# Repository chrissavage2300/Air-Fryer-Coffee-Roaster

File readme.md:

A DIY Coffee roaster based on on air fryer. 

The idea is to have a rotating drum with a heater and fan inside. A nextion display will be used. 

Features:
Adjustable Temp
Adjustable Drum Speed
Adjustable Fan Speed
Cooling and heating modes

Change Log:

The roaster does work, but it has a slight issue when it gets hot where the rotation motor just doesnt turn. From what I can tell, its not a failure of the motor, but a fail in the comms. I have to look into why it does this, as i think its a buffer situation. Everything else works though, so Im not sure why just that gives out. 

10/7/2023- Uploaded Main Code

12/3/2022- Start of this github. But the project dates back a few months atleast

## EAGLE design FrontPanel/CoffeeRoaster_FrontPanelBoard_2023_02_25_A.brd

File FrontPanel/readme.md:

These are the files for the front panel. It mostly works. This communicates with the main panel via USART as it was the only means of communication that was available. 

Latest Version: 6/15/2023

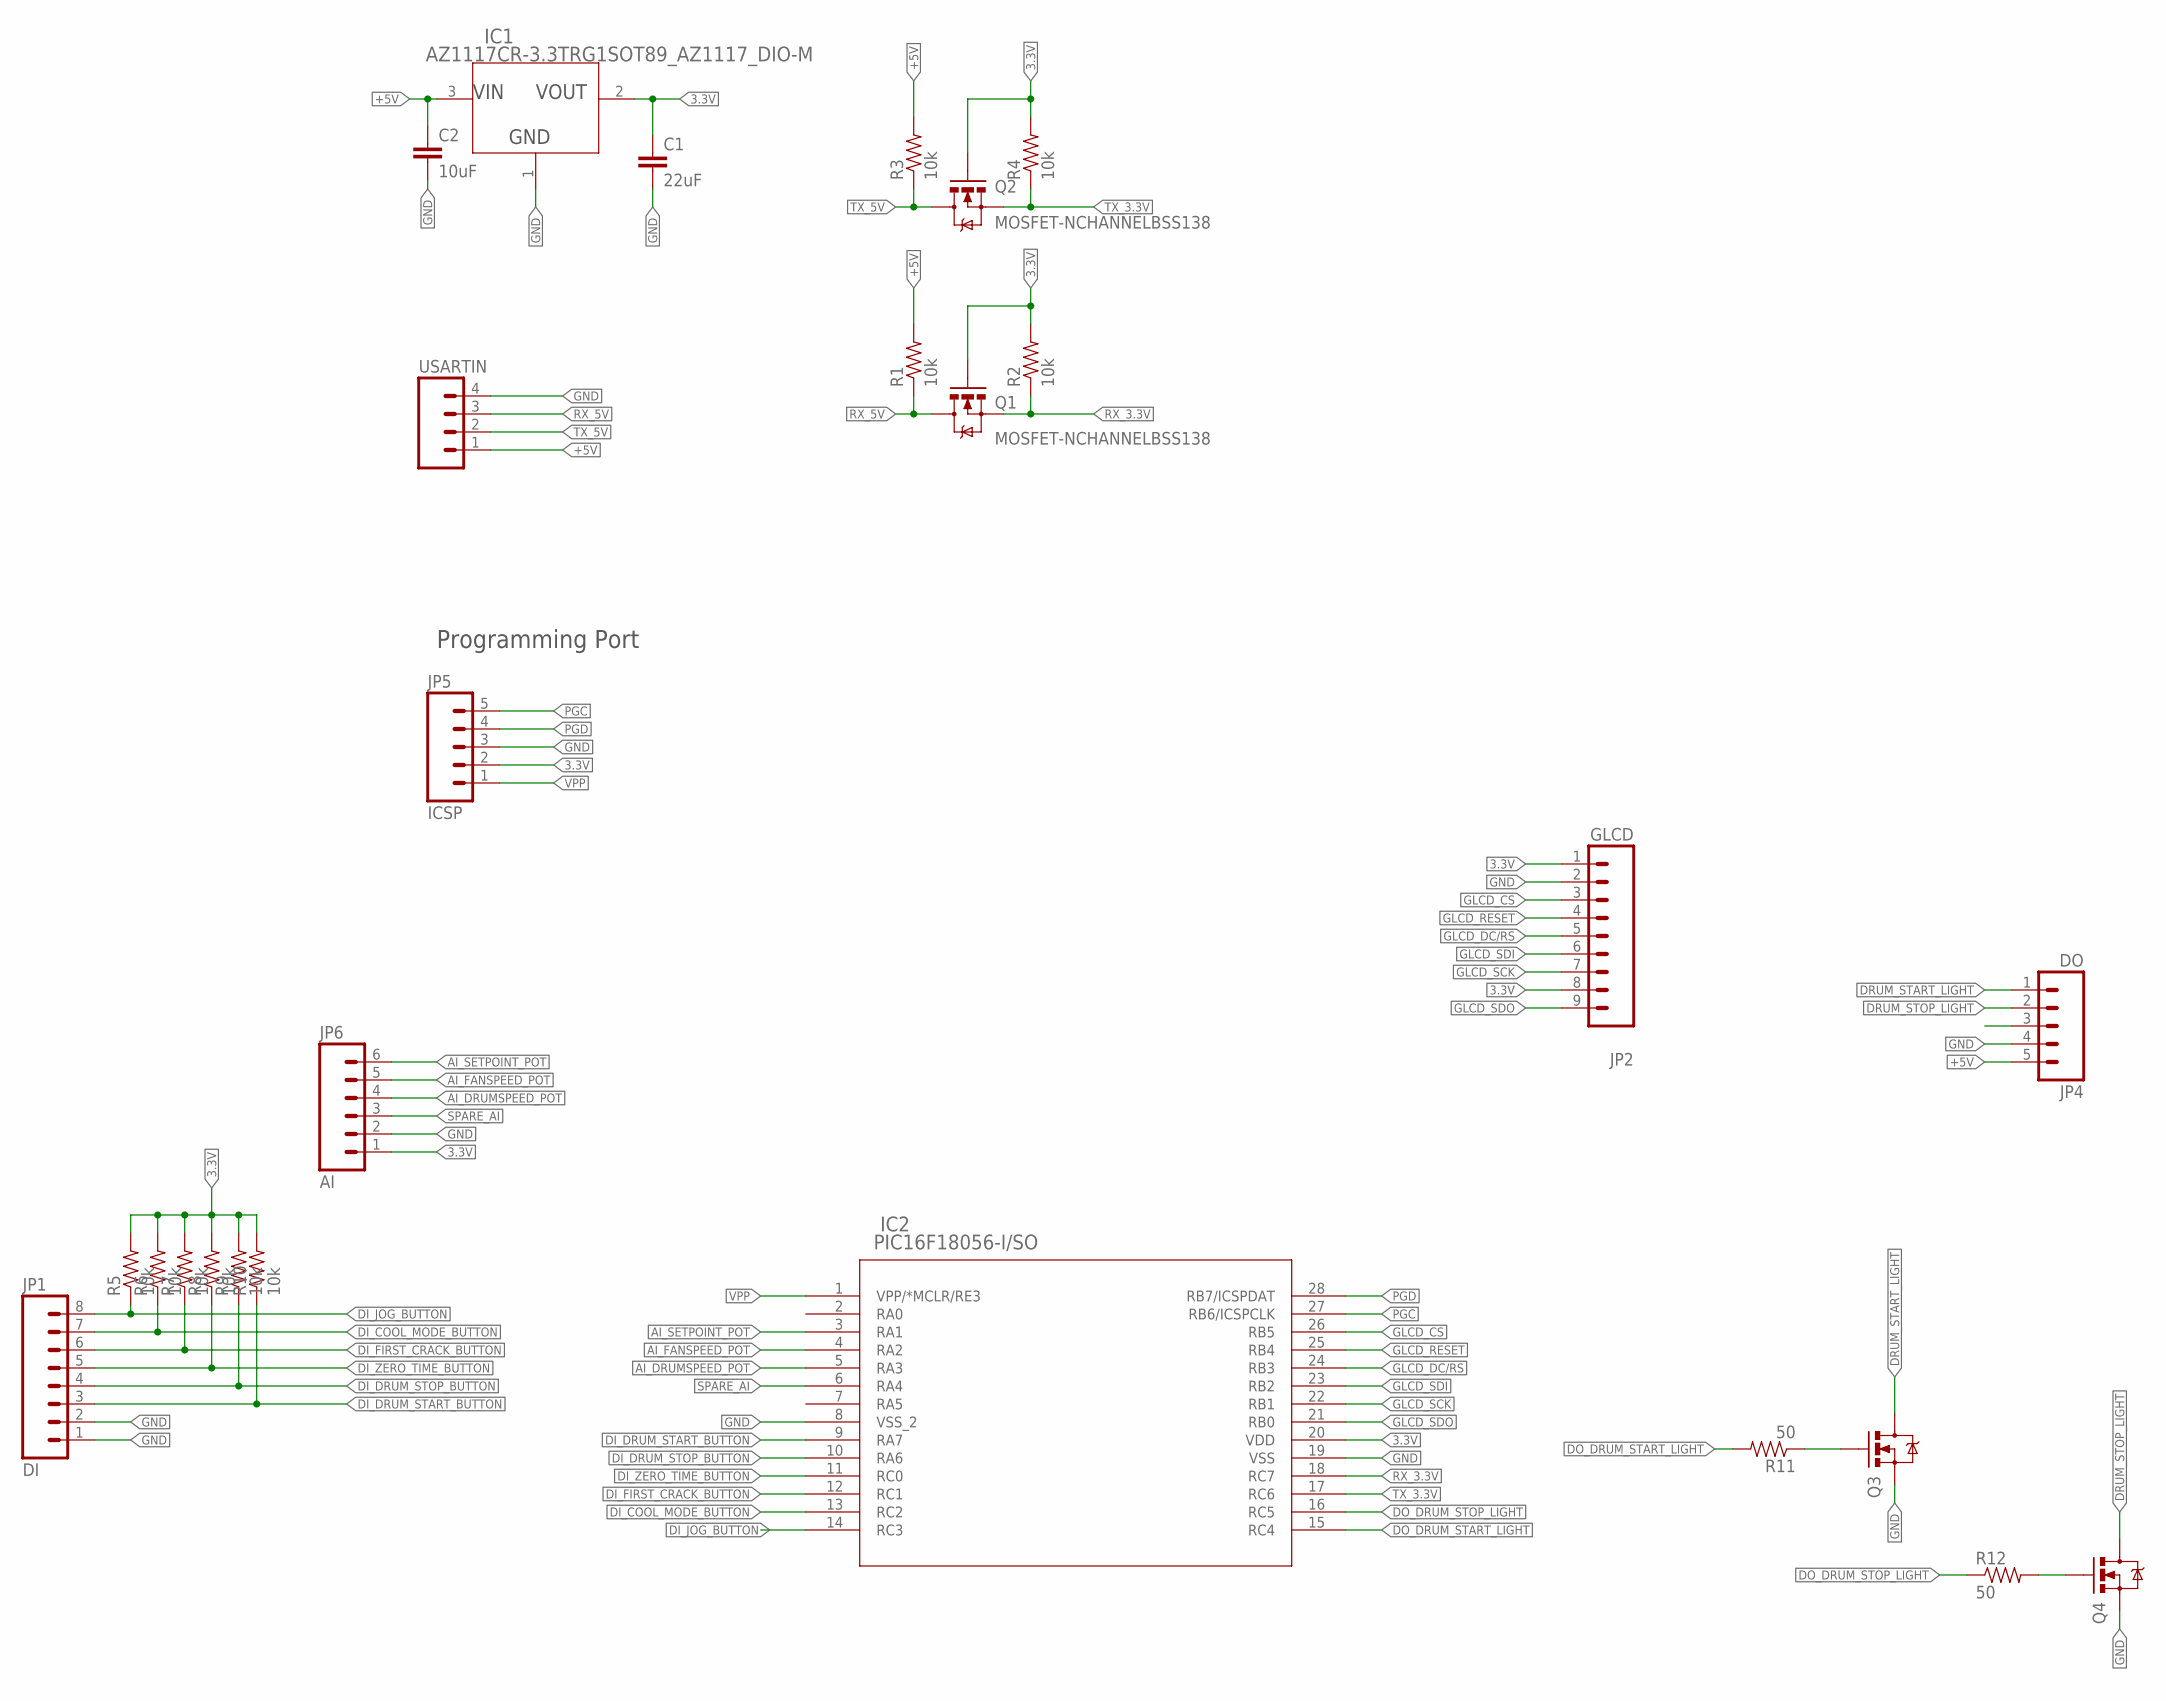
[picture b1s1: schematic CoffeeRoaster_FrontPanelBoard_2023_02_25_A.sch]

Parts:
C1: 22uF; 1206
C2: 10uF; 1206
IC1: AZ1117CR-3.3TRG1SOT89_AZ1117_DIO-M; SOT89_AZ1117_DIO-M
IC2: PIC16F18056-I/SO; SOIC28-W_MC
JP1: DI; 1X08_LOCK_LONGPADS
JP2: GLCD; 1X09_LOCK_LONGPADS
JP4: DO; 1X05_LOCK_LONGPADS
JP5: ICSP; 1X05
JP6: AI; 1X06_LOCK_LONGPADS
Q1, Q2, Q3, Q4: MOSFET-NCHANNELBSS138; SOT23-3
R1, R2, R3, R4, R5, R6, R7, R8, R9, R10: 10k; 1206
R11, R12: 50; 1206
USARTIN: M04LONGPADS; 1X04_LONGPADS

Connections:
3.3V: C1.1, IC1.2 (OUTPUT), IC2.20 (VDD), JP2.1, JP2.8, JP5.2, JP6.1, Q1.1 (G), Q2.1 (G), R2.2, R4.2, R5.2, R6.2, R7.2, R8.2, R9.2, R10.2
+5V: C2.1, IC1.3 (INPUT), JP4.5, R1.2, R3.2, USARTIN.1
AI_DRUMSPEED_POT: IC2.5 (RA3), JP6.4
AI_FANSPEED_POT: IC2.4 (RA2), JP6.5
AI_SETPOINT_POT: IC2.3 (RA1), JP6.6
DI_COOL_MODE_BUTTON: IC2.13 (RC2), JP1.7, R6.1
DI_DRUM_START_BUTTON: IC2.9 (RA7), JP1.3, R10.1
DI_DRUM_STOP_BUTTON: IC2.10 (RA6), JP1.4, R9.1
DI_FIRST_CRACK_BUTTON: IC2.12 (RC1), JP1.6, R7.1
DI_JOG_BUTTON: IC2.14 (RC3), JP1.8, R5.1
DI_ZERO_TIME_BUTTON: IC2.11 (RC0), JP1.5, R8.1
DO_DRUM_START_LIGHT: IC2.15 (RC4), R11.2
DO_DRUM_STOP_LIGHT: IC2.16 (RC5), R12.1
DRUM_START_LIGHT: JP4.1, Q3.3 (D)
DRUM_STOP_LIGHT: JP4.2, Q4.3 (D)
GLCD_CS: IC2.26 (RB5), JP2.3
GLCD_DC/RS: IC2.24 (RB3), JP2.5
GLCD_RESET: IC2.25 (RB4), JP2.4
GLCD_SCK: IC2.22 (RB1), JP2.7
GLCD_SDI: IC2.23 (RB2), JP2.6
GLCD_SDO: IC2.21 (RB0), JP2.9
GND: C1.2, C2.2, IC1.1 (ADJ/GND), IC2.8 (VSS_2), IC2.19 (VSS), JP1.1, JP1.2, JP2.2, JP4.4, JP5.3, JP6.2, Q3.2 (S), Q4.2 (S), USARTIN.4
unnamed: Q3.1 (G), R11.1
unnamed: Q4.1 (G), R12.2
PGC: IC2.27 (RB6/ICSPCLK), JP5.5
PGD: IC2.28 (RB7/ICSPDAT), JP5.4
RX_3.3V: IC2.18 (RC7), Q1.2 (S), R2.1
RX_5V: Q1.3 (D), R1.1, USARTIN.3
SPARE_AI: IC2.6 (RA4), JP6.3
TX_3.3V: IC2.17 (RC6), Q2.2 (S), R4.1
TX_5V: Q2.3 (D), R3.1, USARTIN.2
VPP: IC2.1 (VPP/*MCLR/RE3), JP5.1

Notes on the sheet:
Programming Port

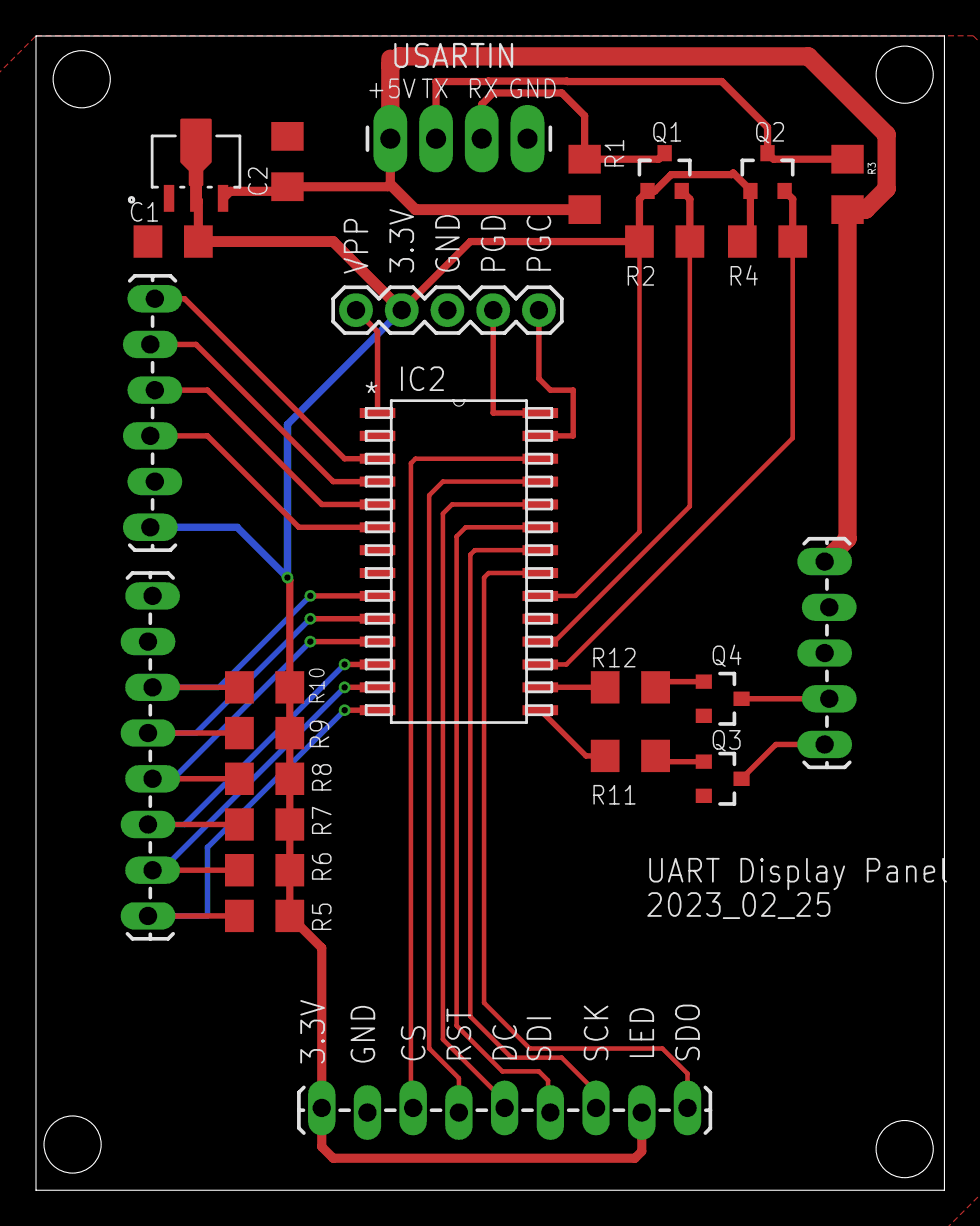
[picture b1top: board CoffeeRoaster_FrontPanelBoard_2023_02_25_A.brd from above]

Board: 2 copper layers, 50.5 x 64.1 mm, 26 parts (0 on the bottom side), 32 nets.

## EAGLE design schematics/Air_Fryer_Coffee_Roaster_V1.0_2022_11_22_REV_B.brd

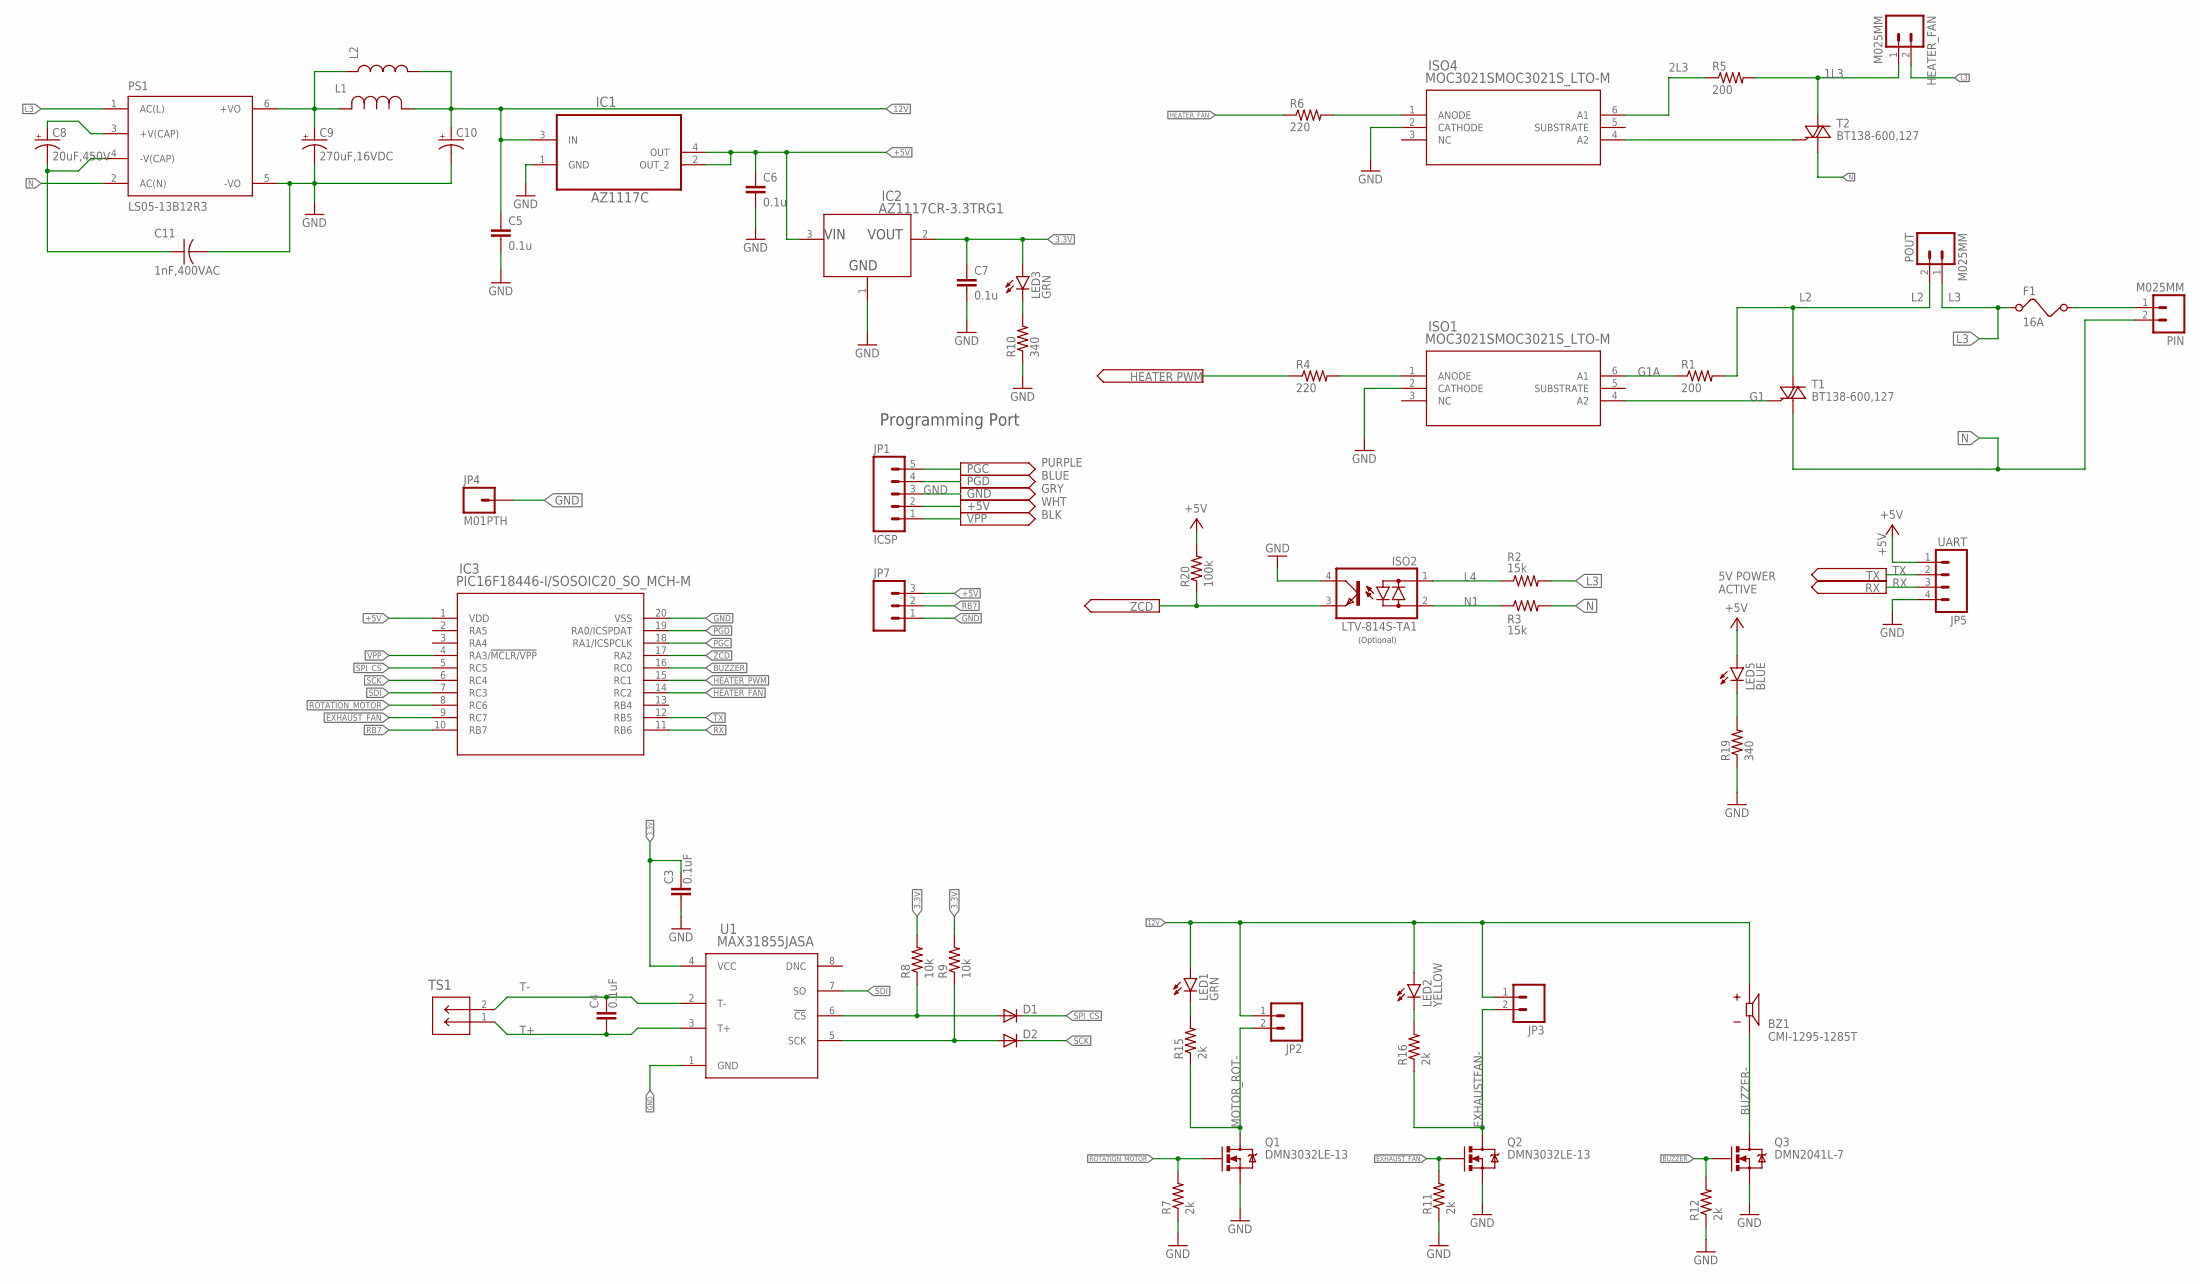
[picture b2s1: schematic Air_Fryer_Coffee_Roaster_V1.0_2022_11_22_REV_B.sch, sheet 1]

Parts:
BZ1: CMI-1295-1285T; CUI_CMI-1295-1285T
C3, C4: 0.1uF; 0805
C5, C6, C7: 0.1u; 1206
C8: 20uF,450V; E5-13
C9: 270uF,16VDC; PANASONIC_E
C10: CAP_POLE; PANASONIC_E
C11: 1nF,400VAC; C050-075X075
D1, D2: DIODESOD-323F; SOD-323F
F1: 16A; FUSE
HEATER_FAN: M025MM; SCREWTERMINAL-5MM-2
IC1: AZ1117C; SOT230P700X180-4N
IC2: AZ1117CR-3.3TRG1; SOT89_AZ1117_DIO
IC3: PIC16F18446-I/SOSOIC20_SO_MCH-M; SOIC20_SO_MCH-M
ISO1, ISO4: MOC3021SMOC3021S_LTO-M; MOC3021S_LTO-M
ISO2: LTV-814S-TA1; DIL4-SMD
JP1: ICSP; 1X05
JP2, JP3: M02POLAR_LOCK; MOLEX-1X2_LOCK
JP4: M01PTH; 1X01
JP5: UART; 1X04_LOCK
JP7: M03LOCK; 1X03_LOCK
L1: 4.7uH, 2.2A; IND_BOURNS_SRR1260
L2: INDUCTORCR54; CR54
LED1, LED3: GRN; LED-1206
LED2: YELLOW; LED-1206
LED5: BLUE; LED-1206
PIN: M025MM; SCREWTERMINAL-5MM-2
POUT: M025MM; SCREWTERMINAL-5MM-2
PS1: LS05-13B12R3; CONV_LS05-13B12R3
Q1, Q2: DMN3032LE-13; SOT223
Q3: DMN2041L-7; SOT23-3
R1, R5: 200; R2512
R2, R3: 15k; R2512
R4, R6: 220; 1206
R7, R11, R12, R15, R16: 2k; 1206
R8, R9: 10k; M0805
R10, R19: 340; 1206
R20: 100k; 1206
T1, T2: BT138-600,127; TO220BV
TS1: YK3210203000G; CONN2_282845-2_TEC
U1: MAX31855JASA; 21-0041B_8_MXM-M

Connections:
1L3: HEATER_FAN.1, R5.2, T2.T2 (A2)
2L3: ISO4.6 (A1), R5.1
3.3V: C3.2, C7.1, IC2.2 (OUTPUT), LED3.A, R8.2, R9.2, U1.4 (VCC)
12V: BZ1.P, C5.1, C10.+, IC1.3 (IN), JP2.1, JP3.1, L1.1, L2.P$2 (2), LED1.A, LED2.A
+5V: C6.1, IC1.2 (OUT_2), IC1.4 (OUT), IC2.3 (INPUT), IC3.1 (VDD), JP1.2, JP5.1, JP7.3, LED5.A, R20.2
BUZZER: IC3.16 (RC0), Q3.1 (G), R12.2
BUZZER-: BZ1.N, Q3.3 (D)
EXHAUSTFAN-: JP3.2, Q2.2 (D), Q2.4 (D), R16.1
EXHAUST_FAN: IC3.9 (RC7), Q2.1 (G), R11.2
G1: ISO1.4 (A2), T1.G
G1A: ISO1.6 (A1), R1.1
GATE_2: ISO4.4 (A2), T2.G
GND: C3.1, C5.2, C6.2, C7.2, C9.-, C10.-, C11.2, IC1.1 (GND), IC2.1 (ADJ/GND), IC3.20 (VSS), ISO1.2 (CATHODE), ISO2.4 (C), ISO4.2 (CATHODE), JP1.3, JP4.1, JP5.4, JP7.1, PS1.5 (-VO), Q1.3 (S), Q2.3 (S), Q3.2 (S), R7.1, R10.1, R11.1, R12.1, R19.1, U1.1 (GND)
HEATER_FAN: IC3.14 (RC2), R6.1
HEATER_PWM: IC3.15 (RC1), R4.1
L1: F1.2, PIN.1
L2: POUT.2, R1.2, T1.T2 (A2)
L3: F1.1, HEATER_FAN.2, POUT.1, PS1.1 (AC(L)), R2.2
L4: ISO2.1 (AC1), R2.1
MOTOR_ROT-: JP2.2, Q1.2 (D), Q1.4 (D), R15.1
N: PIN.2, PS1.2 (AC(N)), R3.2, T1.T1 (A1), T2.T1 (A1)
N1: ISO2.2 (AC2), R3.1
unnamed: ISO1.1 (ANODE), R4.2
unnamed: LED3.C, R10.2
unnamed: LED1.C, R15.2
unnamed: LED2.C, R16.2
unnamed: C8.+, PS1.3 (+V(CAP))
unnamed: C8.-, C11.1, PS1.4 (-V(CAP))
unnamed: ISO4.1 (ANODE), R6.2
unnamed: D1.A, R8.1, U1.6 (!CS)
unnamed: LED5.C, R19.2
unnamed: D2.A, R9.1, U1.5 (SCK)
unnamed: C9.+, L1.2, L2.P$1 (1), PS1.6 (+VO)
PGC: IC3.18 (RA1/ICSPCLK), JP1.5
PGD: IC3.19 (RA0/ICSPDAT), JP1.4
RB7: IC3.10 (RB7), JP7.2
ROTATION_MOTOR: IC3.8 (RC6), Q1.1 (G), R7.2
RX: IC3.11 (RB6), JP5.3
SCK: D2.C, IC3.6 (RC4)
SDI: IC3.7 (RC3), U1.7 (SO)
SPI_CS: D1.C, IC3.5 (RC5)
T+: C4.1, TS1.1, U1.3 (T+)
T-: C4.2, TS1.2, U1.2 (T-)
TX: IC3.12 (RB5), JP5.2
VPP: IC3.4 (RA3/!MCLR/VPP), JP1.1
ZCD: IC3.17 (RA2), ISO2.3 (E), R20.1

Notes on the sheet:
Programming Port
5V POWER ACTIVE
PURPLE BLUE GRY WHT BLK
(Optional)

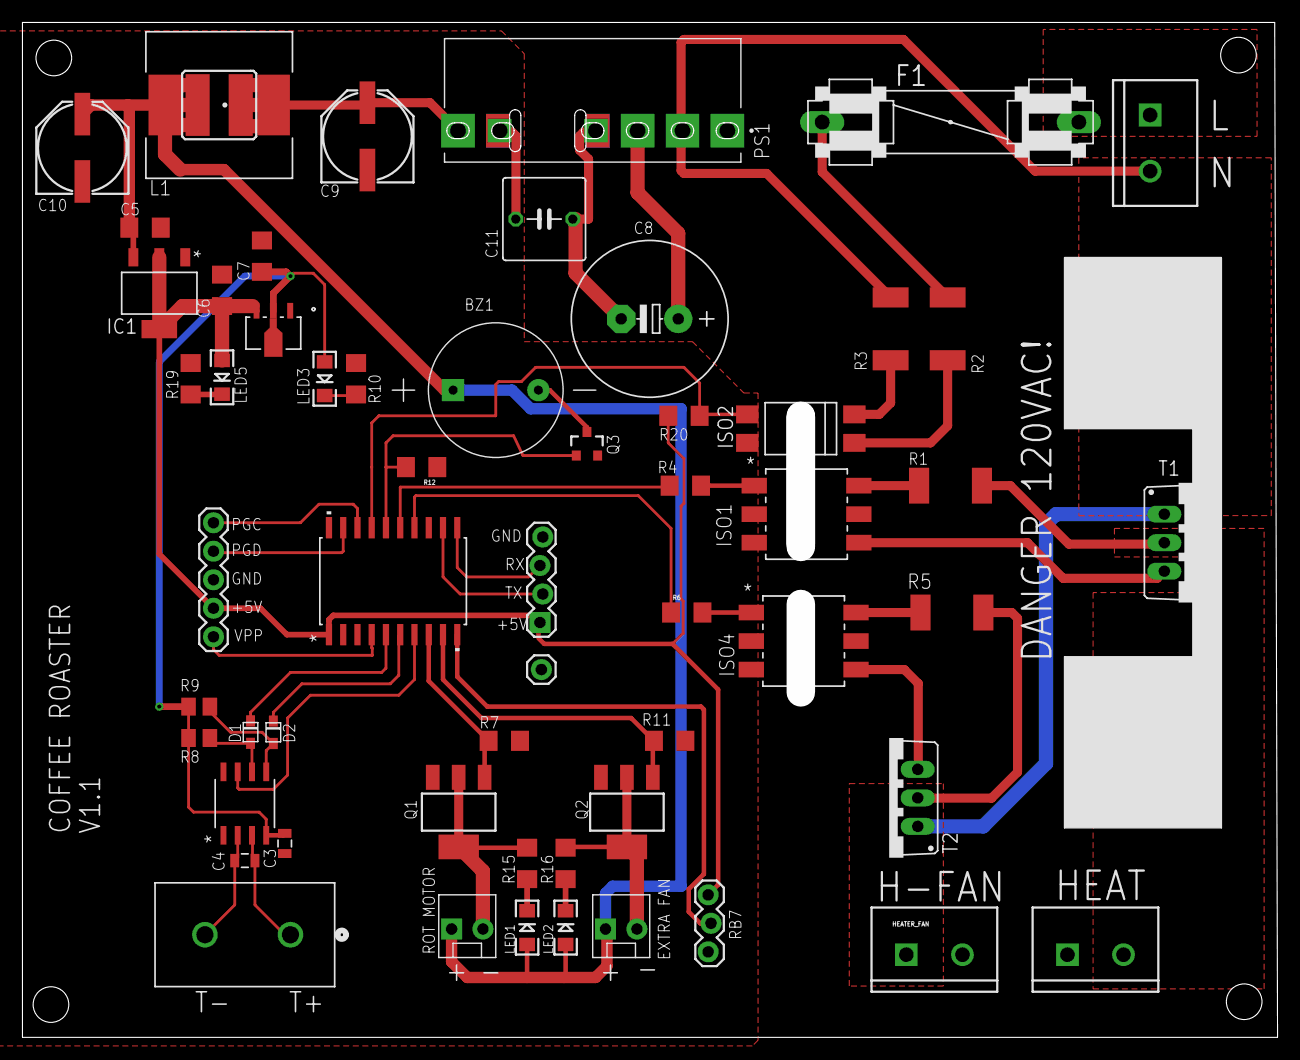
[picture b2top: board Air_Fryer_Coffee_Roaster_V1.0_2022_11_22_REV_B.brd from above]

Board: 2 copper layers, 109.3 x 87.9 mm, 59 parts (0 on the bottom side), 46 nets.

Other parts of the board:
HEATSINK: 7-345-2PP-BA

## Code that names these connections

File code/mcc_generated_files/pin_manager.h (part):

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#define RA2_SetHigh()            do { LATAbits.LATA2 = 1; } while(0)
#define RA2_SetLow()             do { LATAbits.LATA2 = 0; } while(0)
#define RA2_Toggle()             do { LATAbits.LATA2 = ~LATAbits.LATA2; } while(0)
#define RA2_GetValue()              PORTAbits.RA2
#define RA2_SetDigitalInput()    do { TRISAbits.TRISA2 = 1; } while(0)
#define RA2_SetDigitalOutput()   do { TRISAbits.TRISA2 = 0; } while(0)
#define RA2_SetPullup()             do { WPUAbits.WPUA2 = 1; } while(0)
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#define RB5_SetHigh()            do { LATBbits.LATB5 = 1; } while(0)
#define RB5_SetLow()             do { LATBbits.LATB5 = 0; } while(0)
#define RB5_Toggle()             do { LATBbits.LATB5 = ~LATBbits.LATB5; } while(0)
#define RB5_GetValue()              PORTBbits.RB5
#define RB5_SetDigitalInput()    do { TRISBbits.TRISB5 = 1; } while(0)
#define RB5_SetDigitalOutput()   do { TRISBbits.TRISB5 = 0; } while(0)
#define RB5_SetPullup()             do { WPUBbits.WPUB5 = 1; } while(0)
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#define RB6_SetHigh()            do { LATBbits.LATB6 = 1; } while(0)
#define RB6_SetLow()             do { LATBbits.LATB6 = 0; } while(0)
#define RB6_Toggle()             do { LATBbits.LATB6 = ~LATBbits.LATB6; } while(0)
#define RB6_GetValue()              PORTBbits.RB6
#define RB6_SetDigitalInput()    do { TRISBbits.TRISB6 = 1; } while(0)
#define RB6_SetDigitalOutput()   do { TRISBbits.TRISB6 = 0; } while(0)
#define RB6_SetPullup()             do { WPUBbits.WPUB6 = 1; } while(0)
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// get/set BUZZER aliases
#define BUZZER_TRIS                 TRISCbits.TRISC0
#define BUZZER_LAT                  LATCbits.LATC0
#define BUZZER_PORT                 PORTCbits.RC0
#define BUZZER_WPU                  WPUCbits.WPUC0
#define BUZZER_OD                   ODCONCbits.ODCC0
#define BUZZER_ANS                  ANSELCbits.ANSC0
#define BUZZER_SetHigh()            do { LATCbits.LATC0 = 1; } while(0)
#define BUZZER_SetLow()             do { LATCbits.LATC0 = 0; } while(0)
#define BUZZER_Toggle()             do { LATCbits.LATC0 = ~LATCbits.LATC0; } while(0)
#define BUZZER_GetValue()           PORTCbits.RC0
#define BUZZER_SetDigitalInput()    do { TRISCbits.TRISC0 = 1; } while(0)
#define BUZZER_SetDigitalOutput()   do { TRISCbits.TRISC0 = 0; } while(0)
#define BUZZER_SetPullup()          do { WPUCbits.WPUC0 = 1; } while(0)
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// get/set HEATER_PWM aliases
#define HEATER_PWM_TRIS                 TRISCbits.TRISC1
#define HEATER_PWM_LAT                  LATCbits.LATC1
#define HEATER_PWM_PORT                 PORTCbits.RC1
#define HEATER_PWM_WPU                  WPUCbits.WPUC1
#define HEATER_PWM_OD                   ODCONCbits.ODCC1
#define HEATER_PWM_ANS                  ANSELCbits.ANSC1
#define HEATER_PWM_SetHigh()            do { LATCbits.LATC1 = 1; } while(0)
#define HEATER_PWM_SetLow()             do { LATCbits.LATC1 = 0; } while(0)
#define HEATER_PWM_Toggle()             do { LATCbits.LATC1 = ~LATCbits.LATC1; } while(0)
#define HEATER_PWM_GetValue()           PORTCbits.RC1
#define HEATER_PWM_SetDigitalInput()    do { TRISCbits.TRISC1 = 1; } while(0)
#define HEATER_PWM_SetDigitalOutput()   do { TRISCbits.TRISC1 = 0; } while(0)
#define HEATER_PWM_SetPullup()          do { WPUCbits.WPUC1 = 1; } while(0)
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// get/set HEATER_FAN aliases
#define HEATER_FAN_TRIS                 TRISCbits.TRISC2
#define HEATER_FAN_LAT                  LATCbits.LATC2
#define HEATER_FAN_PORT                 PORTCbits.RC2
#define HEATER_FAN_WPU                  WPUCbits.WPUC2
#define HEATER_FAN_OD                   ODCONCbits.ODCC2
#define HEATER_FAN_ANS                  ANSELCbits.ANSC2
#define HEATER_FAN_SetHigh()            do { LATCbits.LATC2 = 1; } while(0)
#define HEATER_FAN_SetLow()             do { LATCbits.LATC2 = 0; } while(0)
#define HEATER_FAN_Toggle()             do { LATCbits.LATC2 = ~LATCbits.LATC2; } while(0)
#define HEATER_FAN_GetValue()           PORTCbits.RC2
#define HEATER_FAN_SetDigitalInput()    do { TRISCbits.TRISC2 = 1; } while(0)
#define HEATER_FAN_SetDigitalOutput()   do { TRISCbits.TRISC2 = 0; } while(0)
#define HEATER_FAN_SetPullup()          do { WPUCbits.WPUC2 = 1; } while(0)
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#define RC3_SetHigh()            do { LATCbits.LATC3 = 1; } while(0)
#define RC3_SetLow()             do { LATCbits.LATC3 = 0; } while(0)
#define RC3_Toggle()             do { LATCbits.LATC3 = ~LATCbits.LATC3; } while(0)
#define RC3_GetValue()              PORTCbits.RC3
#define RC3_SetDigitalInput()    do { TRISCbits.TRISC3 = 1; } while(0)
#define RC3_SetDigitalOutput()   do { TRISCbits.TRISC3 = 0; } while(0)
#define RC3_SetPullup()             do { WPUCbits.WPUC3 = 1; } while(0)
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#define RC4_SetHigh()            do { LATCbits.LATC4 = 1; } while(0)
#define RC4_SetLow()             do { LATCbits.LATC4 = 0; } while(0)
#define RC4_Toggle()             do { LATCbits.LATC4 = ~LATCbits.LATC4; } while(0)
#define RC4_GetValue()              PORTCbits.RC4
#define RC4_SetDigitalInput()    do { TRISCbits.TRISC4 = 1; } while(0)
#define RC4_SetDigitalOutput()   do { TRISCbits.TRISC4 = 0; } while(0)
#define RC4_SetPullup()             do { WPUCbits.WPUC4 = 1; } while(0)
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// get/set CS aliases
#define CS_TRIS                 TRISCbits.TRISC5
#define CS_LAT                  LATCbits.LATC5
#define CS_PORT                 PORTCbits.RC5
#define CS_WPU                  WPUCbits.WPUC5
#define CS_OD                   ODCONCbits.ODCC5
#define CS_ANS                  ANSELCbits.ANSC5
#define CS_SetHigh()            do { LATCbits.LATC5 = 1; } while(0)
#define CS_SetLow()             do { LATCbits.LATC5 = 0; } while(0)
#define CS_Toggle()             do { LATCbits.LATC5 = ~LATCbits.LATC5; } while(0)
#define CS_GetValue()           PORTCbits.RC5
#define CS_SetDigitalInput()    do { TRISCbits.TRISC5 = 1; } while(0)
#define CS_SetDigitalOutput()   do { TRISCbits.TRISC5 = 0; } while(0)
#define CS_SetPullup()          do { WPUCbits.WPUC5 = 1; } while(0)
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#define RC6_SetHigh()            do { LATCbits.LATC6 = 1; } while(0)
#define RC6_SetLow()             do { LATCbits.LATC6 = 0; } while(0)
#define RC6_Toggle()             do { LATCbits.LATC6 = ~LATCbits.LATC6; } while(0)
#define RC6_GetValue()              PORTCbits.RC6
#define RC6_SetDigitalInput()    do { TRISCbits.TRISC6 = 1; } while(0)
#define RC6_SetDigitalOutput()   do { TRISCbits.TRISC6 = 0; } while(0)
#define RC6_SetPullup()             do { WPUCbits.WPUC6 = 1; } while(0)
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// get/set EXHAUST_FAN aliases
#define EXHAUST_FAN_TRIS                 TRISCbits.TRISC7
#define EXHAUST_FAN_LAT                  LATCbits.LATC7
#define EXHAUST_FAN_PORT                 PORTCbits.RC7
#define EXHAUST_FAN_WPU                  WPUCbits.WPUC7
#define EXHAUST_FAN_OD                   ODCONCbits.ODCC7
#define EXHAUST_FAN_ANS                  ANSELCbits.ANSC7
#define EXHAUST_FAN_SetHigh()            do { LATCbits.LATC7 = 1; } while(0)
#define EXHAUST_FAN_SetLow()             do { LATCbits.LATC7 = 0; } while(0)
#define EXHAUST_FAN_Toggle()             do { LATCbits.LATC7 = ~LATCbits.LATC7; } while(0)
#define EXHAUST_FAN_GetValue()           PORTCbits.RC7
#define EXHAUST_FAN_SetDigitalInput()    do { TRISCbits.TRISC7 = 1; } while(0)
#define EXHAUST_FAN_SetDigitalOutput()   do { TRISCbits.TRISC7 = 0; } while(0)
#define EXHAUST_FAN_SetPullup()          do { WPUCbits.WPUC7 = 1; } while(0)
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
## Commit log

2023-10-07 Add files via upload
    Working Code as of 6/15/2023
2023-10-07 Rename readme.me to readme.md
2023-10-07 Create mcc_generated_files

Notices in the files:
code/mcc_generated_files/pin_manager.h:
(c) 2018 Microchip Technology Inc. and its subsidiaries.
parts and their libraries:
SparkFun-Connectors: Licensing: Creative Commons ShareAlike 4.0 International - https://creativecommons.org/licenses/by-sa/4.0
COPYRIGHT: Copyright (C) 2016 Accelerated Designs. All rights reserved
COPYRIGHT: Copyright (C) 2022 Ultra Librarian. All rights reserved.
